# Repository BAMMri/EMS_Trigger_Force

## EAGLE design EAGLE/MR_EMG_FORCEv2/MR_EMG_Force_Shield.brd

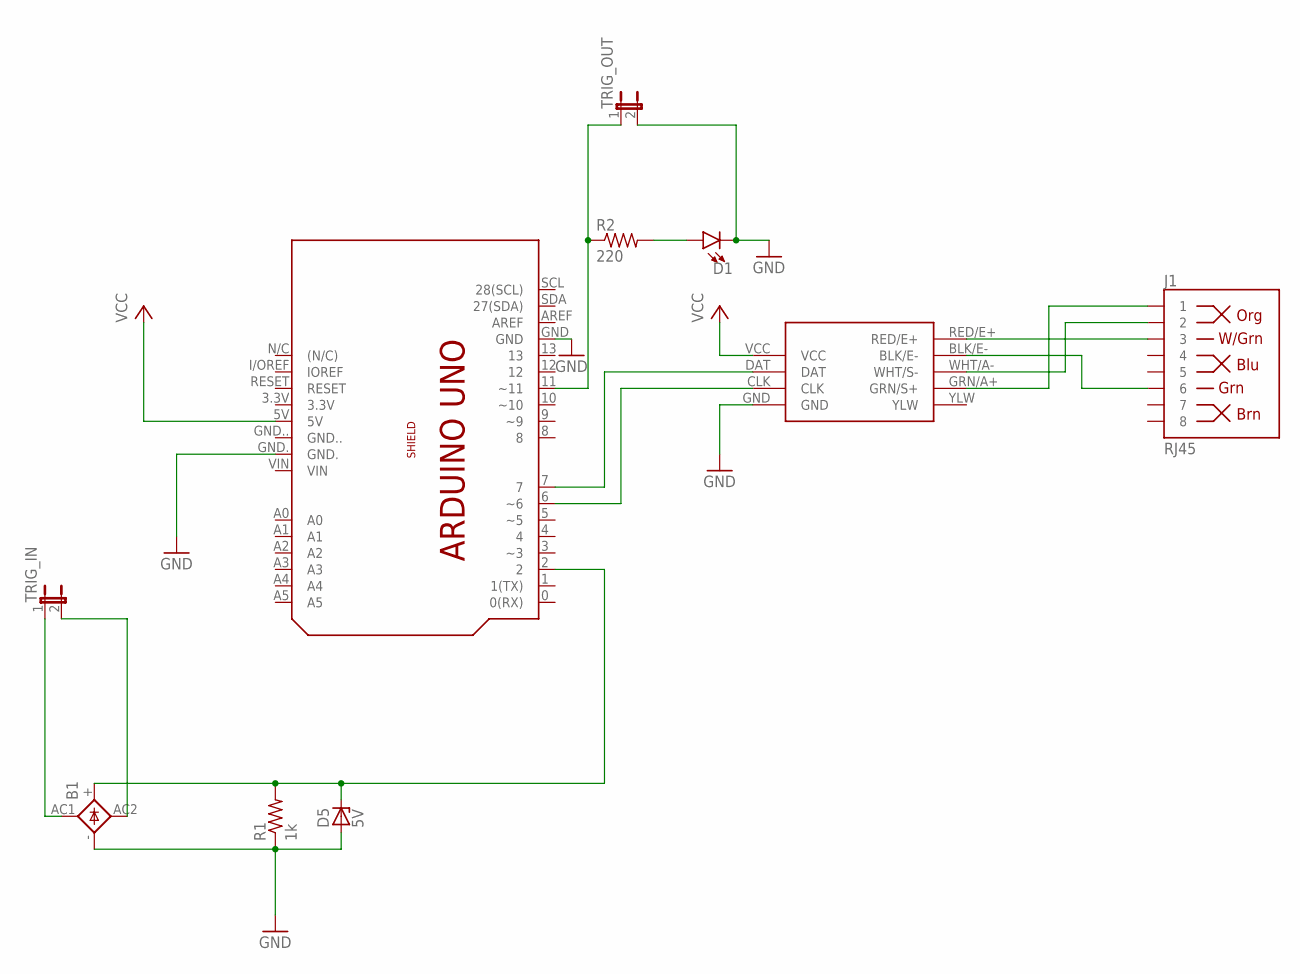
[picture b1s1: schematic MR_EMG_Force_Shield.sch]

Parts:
B1: 1KAB
D1: LED5MM; LED_5MM
D5: 5V; DO41Z10
J1: RJ45; RJ45-8
PCB1: ARDUINO_UNO_SHIELDNOPCB; ARDUINO_UNO_SHIELD_NOPCB
R1: 1k; 0204/7
R2: 220; 0204/7
TRIG_IN: JUMPER-2PTH; 1X02
TRIG_OUT: JUMPER-2PTH; 1X02
U$2: EBAY_HX711_PURPLE; EBAY_HX711_PURPLE_BRD

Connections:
GND: B1.-, D1.K (C), D5.A, PCB1.GND, PCB1.GND., R1.1, TRIG_OUT.2, U$2.GND
unnamed: B1.AC2, TRIG_IN.2
unnamed: B1.AC1, TRIG_IN.1
unnamed: J1.1, U$2.GRN/A+ (GRN/S+)
unnamed: PCB1.6 (~6), U$2.CLK
unnamed: PCB1.7, U$2.DAT
unnamed: J1.2, U$2.WHT/A- (WHT/S-)
unnamed: J1.3, U$2.RED/E+
unnamed: B1.+, D5.C, PCB1.2, R1.2
unnamed: J1.6, U$2.BLK/E-
unnamed: PCB1.11 (~11), R2.1, TRIG_OUT.1
unnamed: D1.A, R2.2
VCC: PCB1.5V, U$2.VCC

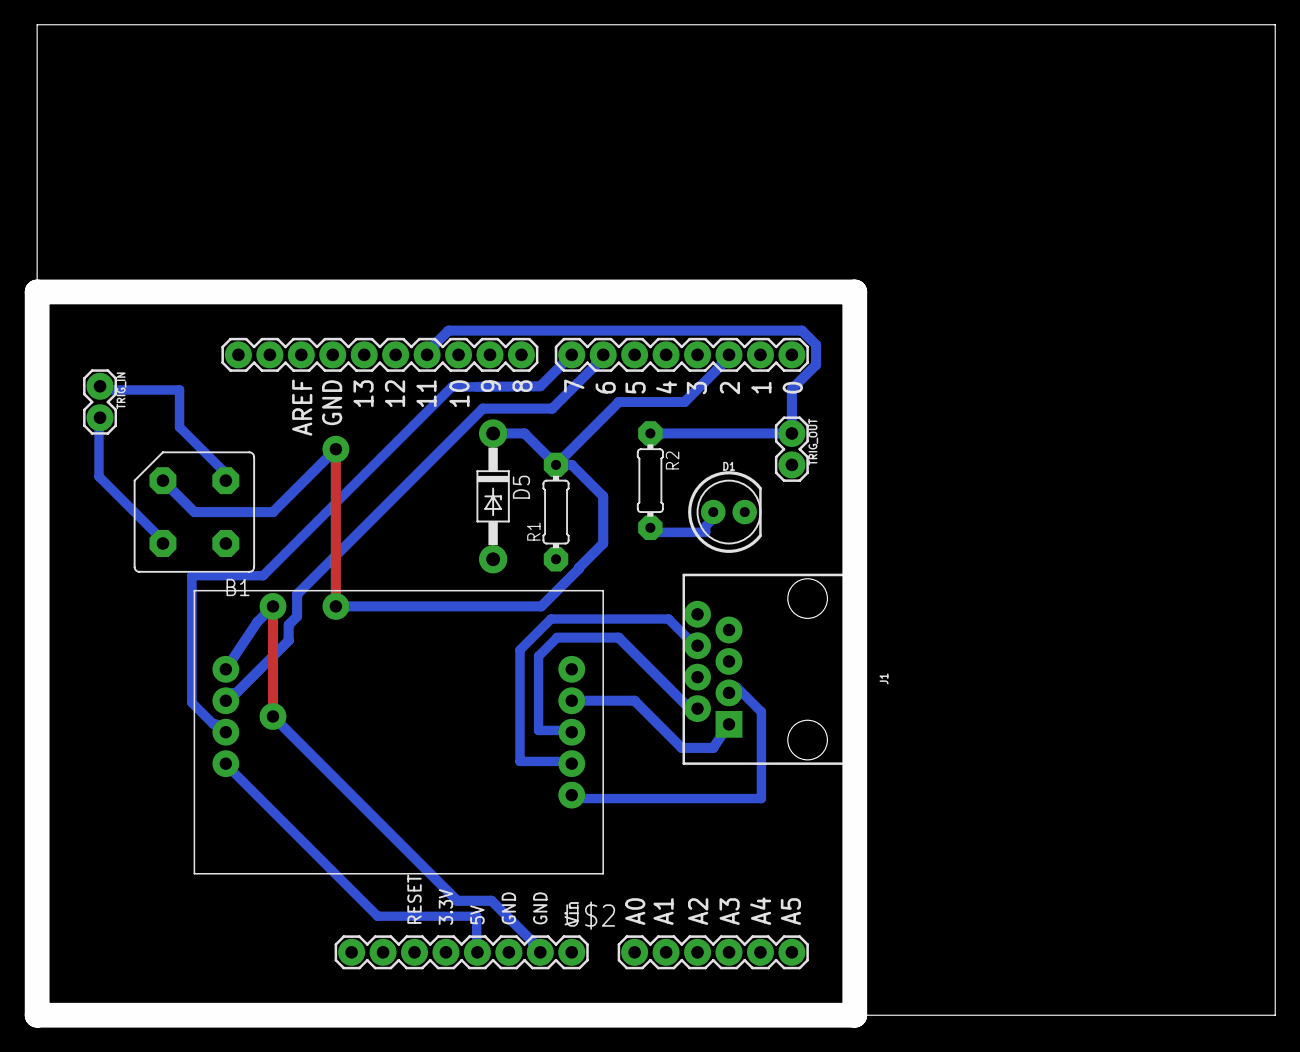
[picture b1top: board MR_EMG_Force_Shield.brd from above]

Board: 2 copper layers, 100.0 x 80.0 mm, 10 parts (0 on the bottom side), 13 nets.

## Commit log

2024-11-12 Current working version
2024-11-13 Multiple scales saved in EEPROM
2024-11-13 Added 7-segment display function
2024-11-13 TM1637 library
2025-01-28 Added schematics

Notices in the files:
parts and their libraries:
SparkFun-Connectors: Licensing: Creative Commons ShareAlike 4.0 International - https://creativecommons.org/licenses/by-sa/4.0
